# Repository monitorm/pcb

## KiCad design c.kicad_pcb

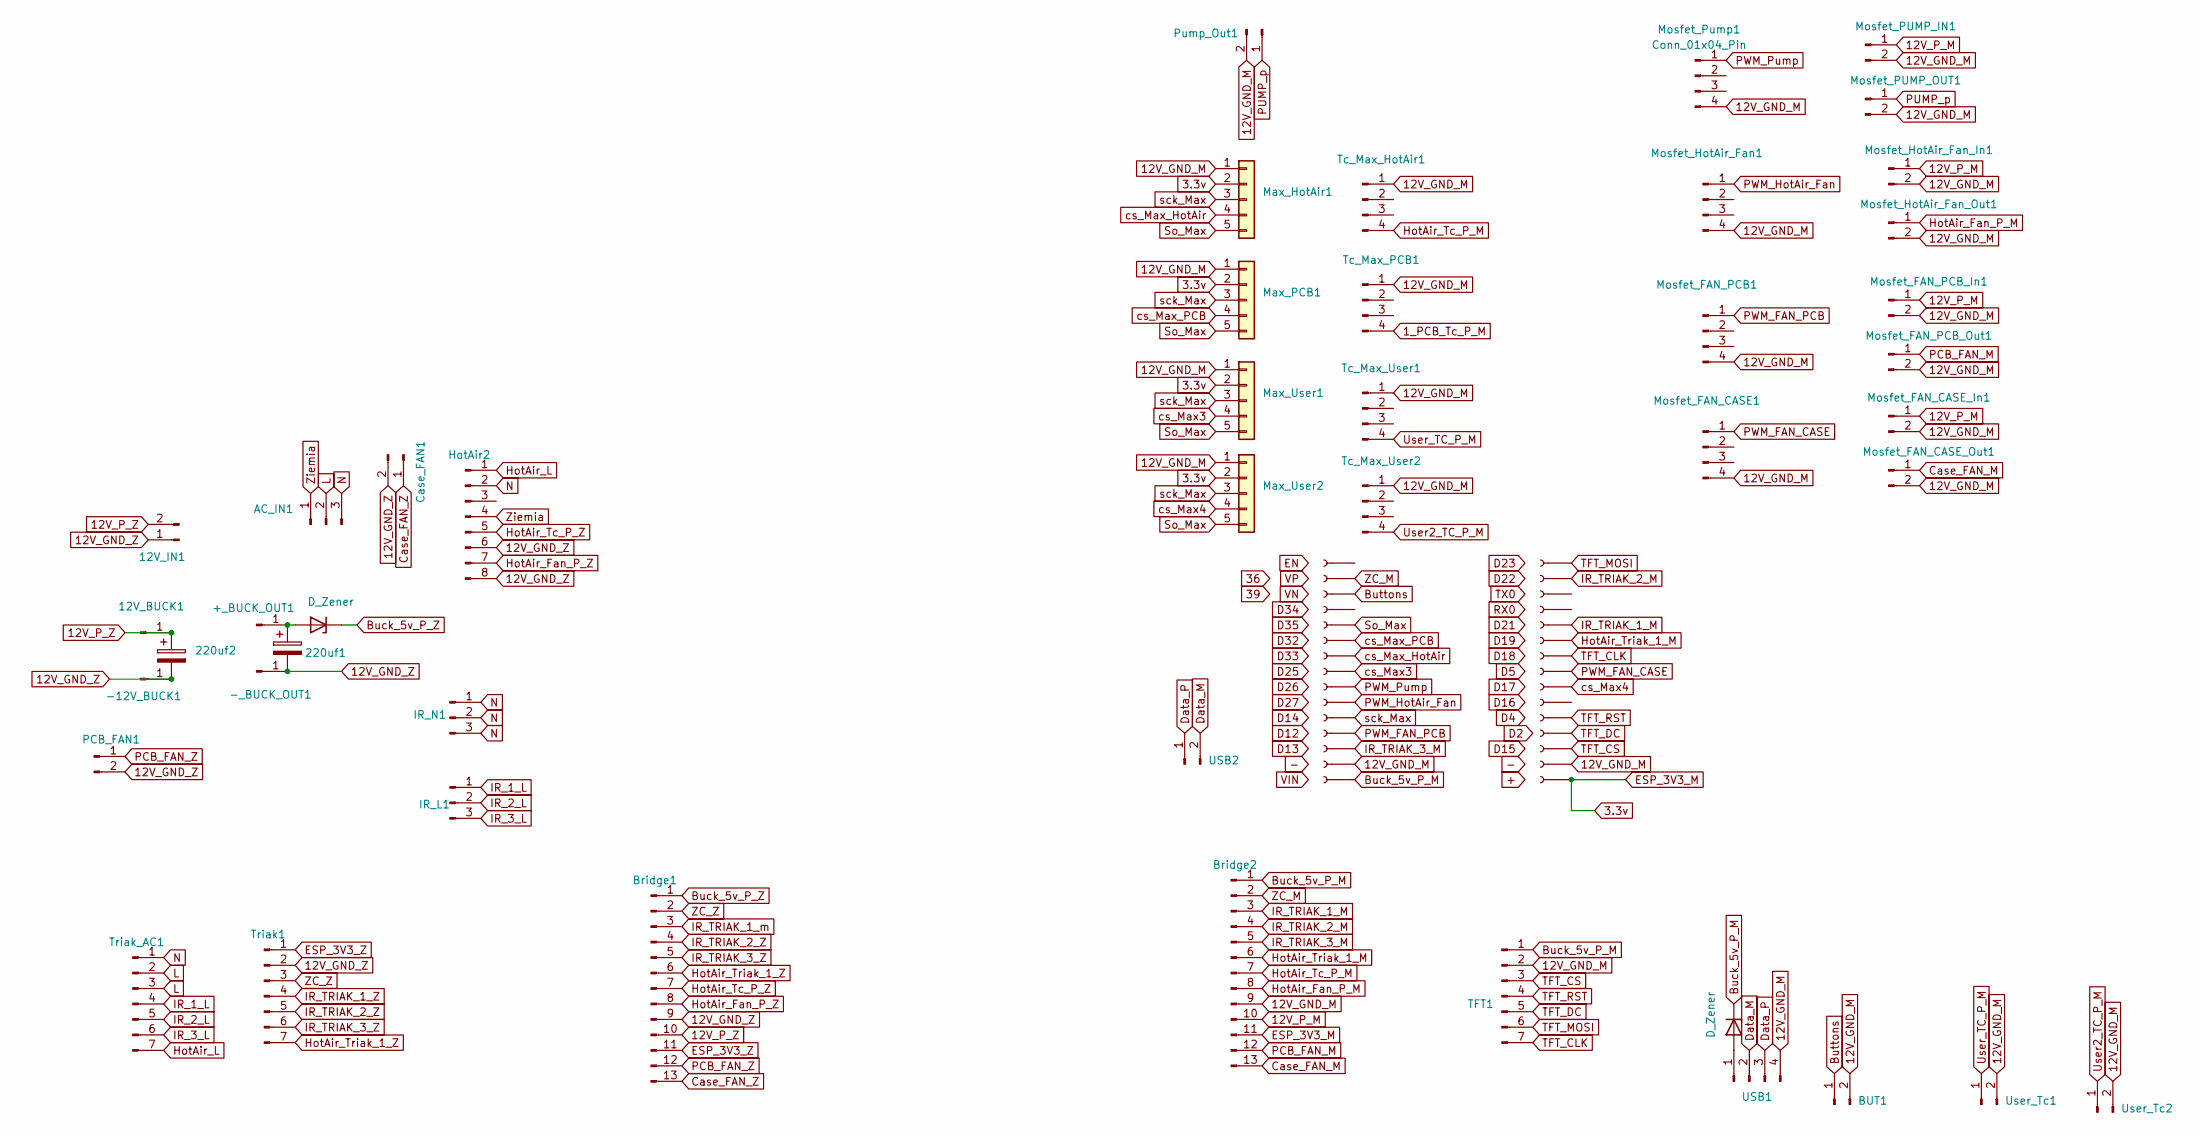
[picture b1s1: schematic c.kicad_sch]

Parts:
12V_BUCK1: Conn_01x01_Pin; PinHeader_1x01_P2.54mm_Vertical
12V_IN1: Conn_01x02_Pin; PinHeader_1x02_P2.54mm_Vertical
220uf1, 220uf2: C_Polarized; CP_Radial_D6.3mm_P2.50mm
+_BUCK_OUT1: Conn_01x01_Pin; PinHeader_1x01_P2.54mm_Vertical
-12V_BUCK1: Conn_01x01_Pin; PinHeader_1x01_P2.54mm_Vertical
-_BUCK_OUT1: Conn_01x01_Pin; PinHeader_1x01_P2.54mm_Vertical
AC_IN1: Conn_01x03_Pin; Samtec_HPM-03-01-x-S_Straight_1x03_Pitch5.08mm
BUT1: Conn_01x02_Pin; PinHeader_1x02_P2.54mm_Vertical
Bridge1, Bridge2: Conn_01x13_Pin; PinHeader_1x13_P2.54mm_Vertical
Case_FAN1: Conn_01x02_Pin; PinHeader_1x02_P2.54mm_Vertical
D1, D2: D_Zener; D_5W_P10.16mm_Horizontal
HotAir2: Conn_01x08_Pin; PinHeader_1x08_P2.54mm_Vertical
IR_L1: Conn_01x03_Pin; Samtec_HPM-03-01-x-S_Straight_1x03_Pitch5.08mm
IR_N1: Conn_01x03_Pin; Samtec_HPM-03-01-x-S_Straight_1x03_Pitch5.08mm
J1, J2: Conn_01x15_Socket; PinHeader_1x15_P2.54mm_Vertical
Max_HotAir1: Conn_01x05; PinHeader_1x05_P2.54mm_Vertical
Max_PCB1: Conn_01x05; PinHeader_1x05_P2.54mm_Vertical
Max_User1, Max_User2: Conn_01x05; PinHeader_1x05_P2.54mm_Vertical
Mosfet_FAN_CASE1: Conn_01x04_Pin; PinHeader_1x04_P2.54mm_Vertical
Mosfet_FAN_CASE_In1: Conn_01x02_Pin; PhoenixContact_MCV_1,5_2-G-5.08_1x02_P5.08mm_Vertical
Mosfet_FAN_CASE_Out1: Conn_01x02_Pin; PhoenixContact_MCV_1,5_2-G-5.08_1x02_P5.08mm_Vertical
Mosfet_FAN_PCB1: Conn_01x04_Pin; PinHeader_1x04_P2.54mm_Vertical
Mosfet_FAN_PCB_In1: Conn_01x02_Pin; PhoenixContact_MCV_1,5_2-G-5.08_1x02_P5.08mm_Vertical
Mosfet_FAN_PCB_Out1: Conn_01x02_Pin; PhoenixContact_MCV_1,5_2-G-5.08_1x02_P5.08mm_Vertical
Mosfet_HotAir_Fan1: Conn_01x04_Pin; PinHeader_1x04_P2.54mm_Vertical
Mosfet_HotAir_Fan_In1: Conn_01x02_Pin; PhoenixContact_MCV_1,5_2-G-5.08_1x02_P5.08mm_Vertical
Mosfet_HotAir_Fan_Out1: Conn_01x02_Pin; PhoenixContact_MCV_1,5_2-G-5.08_1x02_P5.08mm_Vertical
Mosfet_PUMP_IN1: Conn_01x02_Pin; PhoenixContact_MCV_1,5_2-G-5.08_1x02_P5.08mm_Vertical
Mosfet_PUMP_OUT1: Conn_01x02_Pin; PhoenixContact_MCV_1,5_2-G-5.08_1x02_P5.08mm_Vertical
Mosfet_Pump1: Conn_01x04_Pin; PinHeader_1x04_P2.54mm_Vertical
PCB_FAN1: Conn_01x02_Pin; PinHeader_1x02_P2.54mm_Vertical
Pump_Out1: Conn_01x02_Pin; PinHeader_1x02_P2.54mm_Vertical
TFT1: Conn_01x07_Pin; PinHeader_1x07_P2.54mm_Vertical
Tc_Max_HotAir1: Conn_01x04_Pin; PinHeader_1x04_P2.54mm_Vertical
Tc_Max_PCB1: Conn_01x04_Pin; PinHeader_1x04_P2.54mm_Vertical
Tc_Max_User1, Tc_Max_User2: Conn_01x04_Pin; PinHeader_1x04_P2.54mm_Vertical
Triak1: Conn_01x07_Pin; PinHeader_1x07_P2.54mm_Vertical
Triak_AC1: Conn_01x07_Pin; Samtec_HPM-07-01-x-S_Straight_1x07_Pitch5.08mm
USB1: Conn_01x04_Pin; PinHeader_1x04_P2.54mm_Vertical
USB2: Conn_01x02_Pin; PinHeader_1x02_P2.54mm_Vertical
User_Tc1, User_Tc2: Conn_01x02_Pin; PinHeader_1x02_P2.54mm_Vertical

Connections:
1_PCB_Tc_P_M: Tc_Max_PCB1.4
3.3v: Bridge2.11, J1.1, Max_HotAir1.2, Max_PCB1.2, Max_User1.2, Max_User2.2
12V_GND_M: BUT1.2, Bridge2.9, J1.2, J2.2, Max_HotAir1.1, Max_PCB1.1, Max_User1.1, Max_User2.1, Mosfet_FAN_CASE1.4, Mosfet_FAN_CASE_In1.2, Mosfet_FAN_CASE_Out1.2, Mosfet_FAN_PCB1.4, Mosfet_FAN_PCB_In1.2, Mosfet_FAN_PCB_Out1.2, Mosfet_HotAir_Fan1.4, Mosfet_HotAir_Fan_In1.2, Mosfet_HotAir_Fan_Out1.2, Mosfet_PUMP_IN1.2, Mosfet_PUMP_OUT1.2, Mosfet_Pump1.4, Pump_Out1.2, TFT1.2, Tc_Max_HotAir1.1, Tc_Max_PCB1.1, Tc_Max_User1.1, Tc_Max_User2.1, USB1.4, User_Tc1.2, User_Tc2.2
12V_GND_Z: 12V_IN1.1, 220uf1.2, 220uf2.2, -12V_BUCK1.1, -_BUCK_OUT1.1, Bridge1.9, Case_FAN1.2, HotAir2.6, HotAir2.8, PCB_FAN1.2, Triak1.2
12V_P_M: Bridge2.10, Mosfet_FAN_CASE_In1.1, Mosfet_FAN_PCB_In1.1, Mosfet_HotAir_Fan_In1.1, Mosfet_PUMP_IN1.1
12V_P_Z: 12V_BUCK1.1, 12V_IN1.2, 220uf2.1, Bridge1.10
Buck_5v_P_M: Bridge2.1, D2.1 (K), J2.1, TFT1.1
Buck_5v_P_Z: Bridge1.1, D1.1 (K)
Buttons: BUT1.1, J2.13
Case_FAN_M: Bridge2.13, Mosfet_FAN_CASE_Out1.1
Case_FAN_Z: Bridge1.13, Case_FAN1.1
Data_M: USB1.2, USB2.2
Data_P: USB1.3, USB2.1
ESP_3V3_Z: Bridge1.11, Triak1.1
HotAir_Fan_P_M: Bridge2.8, Mosfet_HotAir_Fan_Out1.1
HotAir_Fan_P_Z: Bridge1.8, HotAir2.7
HotAir_L: HotAir2.1, Triak_AC1.7
HotAir_Tc_P_M: Bridge2.7, Tc_Max_HotAir1.4
HotAir_Tc_P_Z: Bridge1.7, HotAir2.5
HotAir_Triak_1_M: Bridge2.6, J1.10
HotAir_Triak_1_Z: Bridge1.6, Triak1.7
IR_1_L: IR_L1.1, Triak_AC1.4
IR_2_L: IR_L1.2, Triak_AC1.5
IR_3_L: IR_L1.3, Triak_AC1.6
IR_TRIAK_1_M: Bridge2.3, J1.11
IR_TRIAK_1_Z: Triak1.4
IR_TRIAK_1_m: Bridge1.3
IR_TRIAK_2_M: Bridge2.4, J1.14
IR_TRIAK_2_Z: Bridge1.4, Triak1.5
IR_TRIAK_3_M: Bridge2.5, J2.3
IR_TRIAK_3_Z: Bridge1.5, Triak1.6
L: AC_IN1.2, Triak_AC1.2, Triak_AC1.3
N: AC_IN1.3, HotAir2.2, IR_N1.1, IR_N1.2, IR_N1.3, Triak_AC1.1
unnamed: 220uf1.1, +_BUCK_OUT1.1, D1.2 (A)
unnamed: D2.2 (A), USB1.1
PCB_FAN_M: Bridge2.12, Mosfet_FAN_PCB_Out1.1
PCB_FAN_Z: Bridge1.12, PCB_FAN1.1
PUMP_p: Mosfet_PUMP_OUT1.1, Pump_Out1.1
PWM_FAN_CASE: J1.8, Mosfet_FAN_CASE1.1
PWM_FAN_PCB: J2.4, Mosfet_FAN_PCB1.1
PWM_HotAir_Fan: J2.6, Mosfet_HotAir_Fan1.1
PWM_Pump: J2.7, Mosfet_Pump1.1
So_Max: J2.11, Max_HotAir1.5, Max_PCB1.5, Max_User1.5, Max_User2.5
TFT_CLK: J1.9, TFT1.7
TFT_CS: J1.3, TFT1.3
TFT_DC: J1.4, TFT1.5
TFT_MOSI: J1.15, TFT1.6
TFT_RST: J1.5, TFT1.4
User2_TC_P_M: Tc_Max_User2.4, User_Tc2.1
User_TC_P_M: Tc_Max_User1.4, User_Tc1.1
ZC_M: Bridge2.2, J2.14
ZC_Z: Bridge1.2, Triak1.3
Ziemia: AC_IN1.1, HotAir2.4
cs_Max3: J2.8, Max_User1.4
cs_Max4: J1.7, Max_User2.4
cs_Max_HotAir: J2.9, Max_HotAir1.4
cs_Max_PCB: J2.10, Max_PCB1.4
sck_Max: J2.5, Max_HotAir1.3, Max_PCB1.3, Max_User1.3, Max_User2.3

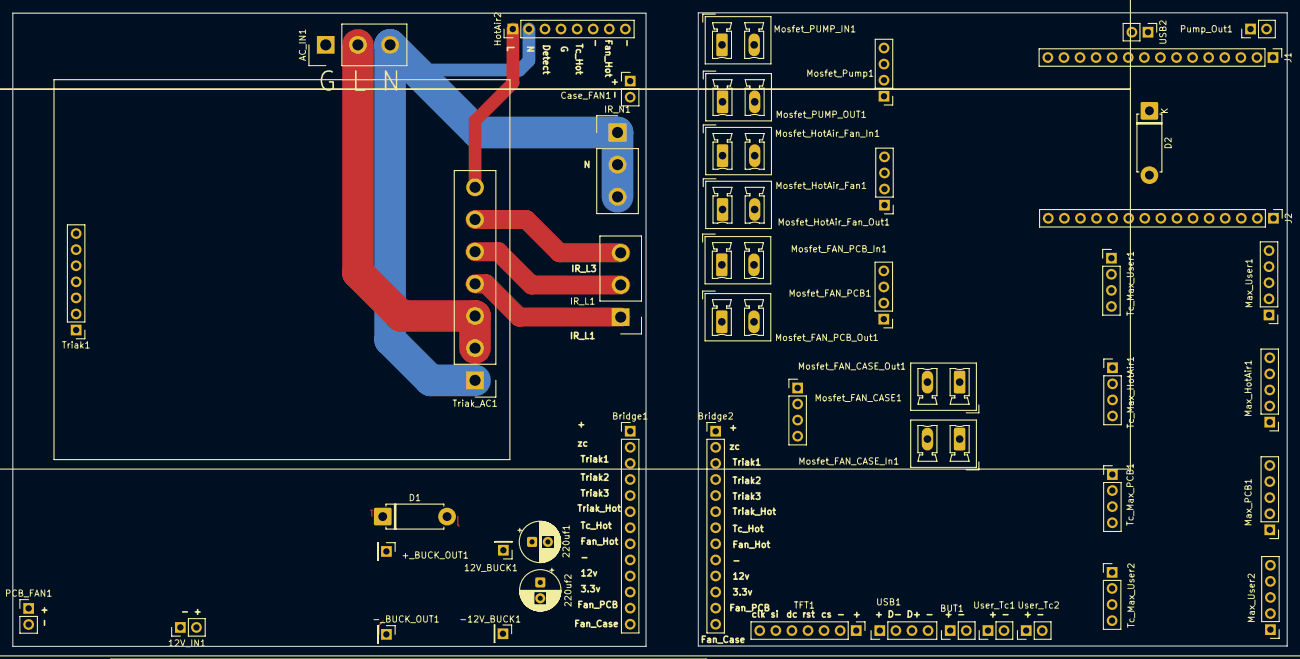
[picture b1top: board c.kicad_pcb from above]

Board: 2 copper layers, 201.3 x 100.1 mm, 48 parts (0 on the bottom side), 55 nets.
